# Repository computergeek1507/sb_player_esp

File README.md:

# ESP32-P4 SB Player

An FSEQ sequence player for the ESP32-P4 that drives holiday and animated light displays. Reads `.fseq` v2 files from an SD card and streams channel data out over E1.31 (sACN) and/or DDP to LED controllers, with synchronized audio playback and a time-based scheduler.

## Downloads

Rolling builds of `main`, updated automatically by GitHub Actions on every push:

- **Firmware** - [firmware-latest](https://github.com/computergeek1507/sb_player_esp/releases/tag/firmware-latest): `SBPlayer.ino.bin` (update), `littlefs.bin` (web pages), `SBPlayer.ino.merged.bin` (first flash over USB)
- **SB Card Builder** - [builder-latest](https://github.com/computergeek1507/sb_player_esp/releases/tag/builder-latest): Flutter and Qt Windows apps, and the Python script; the web version is at <https://computergeek1507.github.io/sb_player_esp/>

## Features

- **FSEQ v2 playback** — reads uncompressed sequences from SD card, frame-accurate timing via FreeRTOS tasks
- **E1.31 (sACN) output** — up to 8 outputs, unicast or multicast, configurable universe/channel mapping
- **DDP output** — up to 8 outputs with per-output channel mapping
- **Audio playback** — WAV and MP3 via I2S DAC (PCM5102A / UDA1334A), auto-matched from sequence media field
- **MultiSync** — master mode to keep secondary players frame-synced
- **Scheduler** — time-windowed autoplay with named playlists; repeat and shuffle support
- **Wired Ethernet** — DHCP or static IP; NTP time sync
- **WiFi AP** — always-on access point for configuration (`SB-Player` / `sbplayer` by default)
- **Web UI** — browser-based management for config, outputs, sequences, playlists, schedule, and OTA firmware updates
- **OLED status display** — 128×64 SSD1306 shows IP, current sequence, frame progress, FPS, and audio state
- **RTC support** — DS3231, DS1307, or PCF8523 for accurate scheduling without NTP; NTP writes back to RTC on first sync

## Repository Layout

```
firmware/SBPlayer/       Arduino sketch and headers
  SBPlayer.ino           Main sketch: setup, playback task, audio task, loop
  config.h               Device config struct + JSON load/save
  fseq.h                 FSEQ v2 parser
  audio.h                I2S audio player (WAV/MP3)
  e131.h                 E1.31/sACN sender
  ddp.h                  DDP sender
  multisync.h            FPP MultiSync master
  scheduler.h            Time-based scheduler + playlist engine
  oled.h                 SSD1306 OLED driver
  rtc.h                  RTC abstraction (DS3231/DS1307/PCF8523)
  sdupdate.h             Firmware / web pages update from the SD card at boot
  webui.h                Async HTTP + WebSocket API and web UI
  data/                  LittleFS web pages (config, outputs, sequences,
                          playlists, schedule, OTA)

hardware/                KiCad ( PCB project (ESP32-P4 + OLED, I2S audio and RTC carrier)
  ESP32-P4_OLED.*        Schematic, PCB, project files
  jlcpcb/                JLCPCB-ready gerbers, BOM, and CPL

tools/                   SB Card Builder (prepares the SD card from xLights)
  sb_card_builder.py     Python / Tkinter version (GUI + command line)
  sb_card_builder_flutter/  Flutter version (Windows desktop and web)
  sb_card_builder_qt/    C++ / Qt 6 version (GUI + command line)
  icon/                  App icon and the script that generates it
```

## Hardware

The carrier board breaks out:

| Connector | Purpose |
|-----------|---------|
| J1 (2×13) | ESP32-P4 module |
| J2 (1×4)  | I2C OLED (SSD1306) |
| J3 (1×6)  | I2S DAC (UDA1334A pin-compatible) |
| J4 (1×6)  | I2S DAC (PCM5102A pin-compatible) |
| U3        | PCF8523T RTC with 32.768 kHz crystal |
| U2        | CR1220 RTC battery backup |

Production files for JLCPCB are in `hardware/jlcpcb/`.

## Firmware Setup

**Board**: `esp32:esp32:esp32p4` (Arduino ESP32 core 3.x)

**Required libraries** (install via Arduino Library Manager or clone into `~/Arduino/libraries`):
- ESP Async WebServer (ESP32Async) and Async TCP
- ArduinoJson
- ESP8266Audio (provides `AudioFileSourceSD`, `AudioGeneratorWAV/MP3`, `AudioOutputI2S`; supports ESP32)
- Adafruit GFX Library
- Adafruit SSD1306
- RTClib

The GitHub Actions workflow `.github/workflows/firmware.yml` builds the firmware with arduino-cli (ESP32 core 3.3.8, default partition scheme) and a `littlefs.bin` of the web pages; both are attached to each run as the `SBPlayer-firmware` download.

**Build and flash**:
1. Open `firmware/SBPlayer/SBPlayer.ino` in Arduino IDE
2. Select board `ESP32P4 Dev Module` and your port
3. Flash the sketch
4. Flash the LittleFS filesystem image (`littlefs.bin`) using the ESP32 LittleFS upload tool — this deploys the web UI pages

## SD Card Layout

```
/sequences/      FSEQ v2 sequence files + matching audio (*.wav / *.mp3)
/playlists/      JSON playlist files
schedule.json    Active schedule (created/managed via web UI)
firmware.bin     Optional firmware update (SBPlayer.ino.bin), installed at boot
littlefs.bin     Optional web pages update (LittleFS image), installed at boot
update.log       Result of each update the player installed from the card
```

**Updating from the SD card** — at boot the player flashes `/littlefs.bin` and then `/firmware.bin` if they are on the card, renames each to `*.installed.bin` (or `*.failed.bin`, so a bad file is only tried once), appends the result to `/update.log` and restarts. `config.json` and `outputs.json` are kept across a web pages update. Use `SBPlayer.ino.bin`, not `SBPlayer.ino.merged.bin` (the merged image is for a full USB flash). The SB Card Builder's *Player update* tab, or `--firmware` / `--littlefs` on the command line, checks the files and copies them to the card. Updates can also be uploaded over the network from `/ota.html`.

Example `schedule.json`:
```json
{
  "entries": [
    { "days": 127, "start_hour": 18, "start_min": 0,
      "end_hour": 23, "end_min": 0, "playlist": "default.json" }
  ]
}
```

Example `playlists/default.json`:
```json
{ "repeat": true, "shuffle": false, "entries": ["show1.fseq", "show2.fseq"] }
```

## SB Card Builder

`tools/sb_card_builder.py` prepares the SD card from an xLights show folder (Python 3.9+, Tkinter):

```
python tools/sb_card_builder.py                                   # GUI
python tools/sb_card_builder.py --show <show folder> --out <SD>   # command line
```

- **Outputs** — reads `xlights_networks.xml` and writes `outputs.json` (E1.31 and DDP controllers). The player imports this file from the card on the next boot and renames it to `outputs.imported.json`.
- **Sequences** — converts xLights `.fseq` files (zstd / zlib compressed, sparse, v1 or v2) to the uncompressed FSEQ v2 the player reads, and copies the matching `.mp3` / `.wav` into `/sequences`.
- **Playlists / Schedule** — builds `playlists/*.json` and `schedule.json`.
- **Player update** — copies a firmware image (`SBPlayer.ino.bin`) and/or web pages image (`littlefs.bin`) to the card root, after checking that each is the right kind of image for the ESP32-P4; the player installs them at its next boot. Command line: `--firmware <bin>` and `--littlefs <bin>` with `--out`.
- **SB Pixel 16 export** — writes sequences for an [SB Pixel 16](https://github.com/computergeek1507/sb_pixel_16) controller instead: pick it under *Export for* on the Sequences tab, or use `--pixel16 <controller name>` with `--show` and `--out`. Each file holds only that controller's channels, uncompressed, in `/sequences`; no audio, `outputs.json`, playlists or schedule are written, because that controller just loops the folder. For an E1.31 controller (or DDP without *Keep Channel Numbers*) the channels are renumbered from 1, matching the port start channels used for E1.31. For DDP with *Keep Channel Numbers* they keep their xLights numbers (stored as one sparse range). The controller buffers at most 262,144 channels per frame and plays the first 64 files.

zstd-compressed sequences (the xLights default) need `python -m pip install zstandard` on Python older than 3.14.

The same tool also exists in two other forms. All three write identical files.

**Flutter (Windows desktop and web)** — `tools/sb_card_builder_flutter`, needs the Flutter SDK:

```
cd tools/sb_card_builder_flutter
flutter run -d windows            # or: flutter build windows  -> build\windows\x64\runner\Release\
flutter run -d chrome             # or: flutter build web      -> build\web\
```

The web build reads and writes folders through the File System Access API, so it needs Chrome or Edge on a computer, served from `localhost` or https. The Flutter app uses the same dark color scheme as the player's web UI.

The web version is deployed to GitHub Pages by `.github/workflows/sb_card_builder_flutter.yml` on every push to `main` that changes the Flutter app: <https://computergeek1507.github.io/sb_player_esp/>.

To host the web build on your own web server instead:

```
flutter build web --release --base-href /sbcard/   # path it will be served from; omit for the site root
```

Copy everything in `build\web\` to that path on the server. The server must use https, and should serve `.wasm` as `application/wasm`. Send `index.html`, `flutter_bootstrap.js` and `flutter_service_worker.js` with `Cache-Control: no-cache` so visitors get new versions after an upload.

**C++ (Qt 6 Widgets)** — `tools/sb_card_builder_qt`, needs Qt 6, CMake 3.21+ and a C++17 compiler; zstd, nlohmann/json and pugixml are downloaded during configure:

```
cd tools/sb_card_builder_qt
cmake -S . -B build -DCMAKE_PREFIX_PATH=<Qt kit, e.g. D:/Qt/6.8.3/msvc2022_64>
cmake --build build --config Release
build\Release\sb_card_builder.exe                               # GUI
build\Release\sb_card_cli.exe --show <show folder> --out <SD>   # command line
```

## Default Pin Assignments

| Function | GPIO |
|----------|------|
| I2S BCLK | 26 |
| I2S LRCLK | 25 |
| I2S DATA | 22 |
| OLED SDA / RTC SDA | 7 |
| OLED SCL / RTC SCL | 8 |
| Ethernet PHY addr | 1 |
| Ethernet MDC | 31 |
| Ethernet MDIO | 52 |
| Ethernet power | 51 |

All pins are configurable via the web UI.

## Web UI Endpoints

| Path | Description |
|------|-------------|
| `/` | Dashboard — playback status, play/stop |
| `/config.html` | Device settings (network, audio, RTC, hostname) |
| `/outputs.html` | E1.31 and DDP output configuration |
| `/sequences.html` | Browse and play sequences from SD |
| `/playlists.html` | Manage playlists |
| `/schedule.html` | Time-based schedule editor |
| `/ota.html` | OTA firmware update |
| `/api/status` | JSON playback status (also pushed via WebSocket `/ws`) |

## License

[CC BY-NC 4.0](LICENSE) — free for personal and non-commercial use; commercial use is not permitted.

## First Boot

1. Connect to the `SB-Player` WiFi AP (password `sbplayer`)
2. Open `http://192.168.4.1` in a browser
3. Configure Ethernet, NTP timezone, output universes, and I2S pins
4. Copy sequences to the SD card and create a playlist
5. Add a schedule entry or play sequences manually from the UI

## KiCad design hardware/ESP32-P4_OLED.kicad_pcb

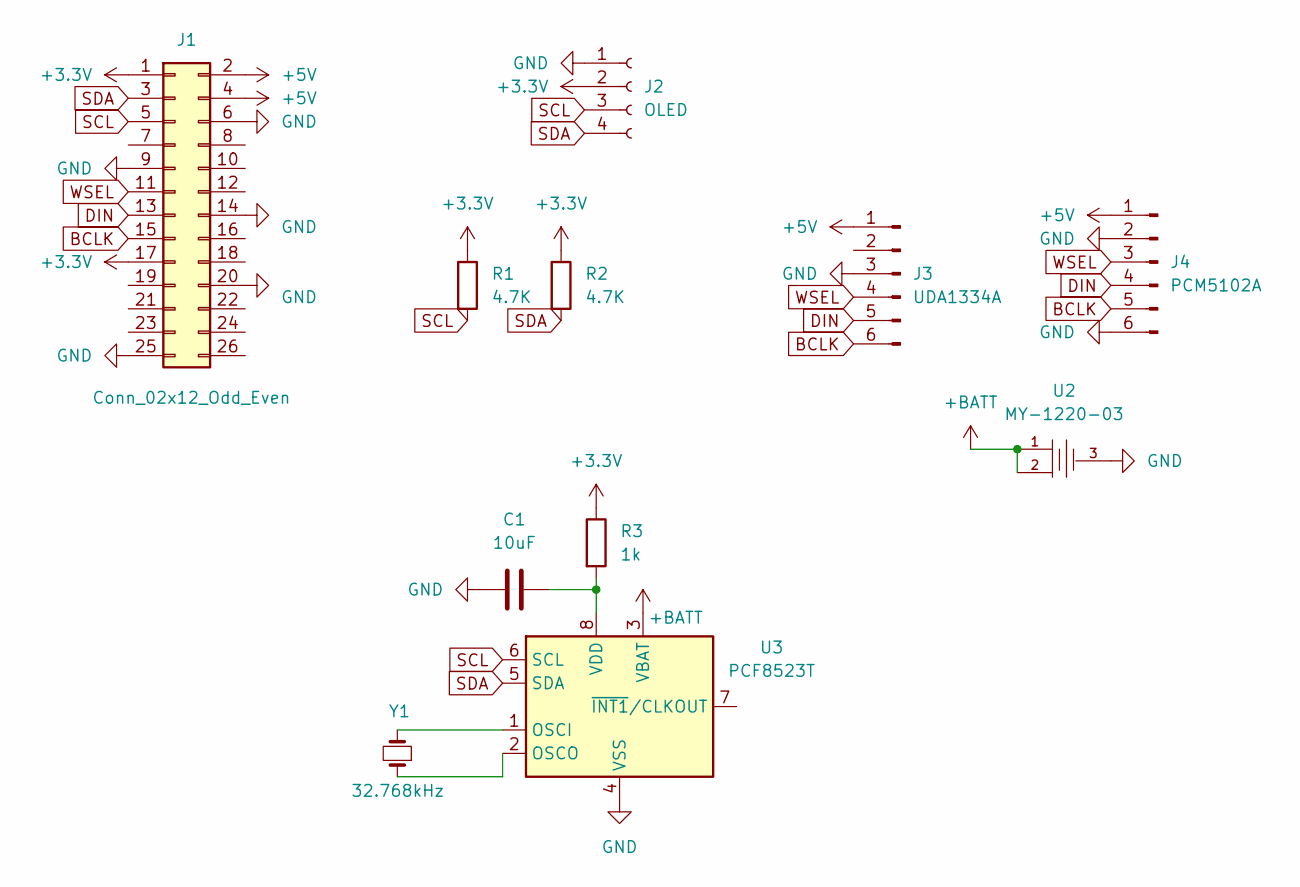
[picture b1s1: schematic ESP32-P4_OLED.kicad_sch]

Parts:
C1: 10uF; C_0805_2012Metric
J1: Conn_02x12_Odd_Even; PinSocket_2x13_P2.54mm_Vertical
J2: OLED; PinSocket_1x04_P2.54mm_Vertical
J3: UDA1334A; PinHeader_1x06_P2.54mm_Vertical
J4: PCM5102A; PinHeader_1x06_P2.54mm_Vertical
R1, R2: 4.7K; R_0603_1608Metric
R3: 1k; R_0603_1608Metric
U2: MY-1220-03; BAT-SMD_MY-1220-03; LCSC C964818
U3: PCF8523T; SOIC-8_3.9x4.9mm_P1.27mm
Y1: 32.768kHz; FC-135R_L3.2-W1.5

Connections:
+3.3V: J1.1, J1.17, J2.2, R1.1, R2.1, R3.1
+5V: J1.2, J1.4, J3.1, J4.1
+BATT: U2.1 (+), U2.2 (+), U3.3 (VBAT)
BCLK: J1.15, J3.6, J4.5
DIN: J1.13, J3.5, J4.4
GND: C1.1, J1.6, J1.9, J1.14, J1.20, J1.25, J2.1, J3.3, J4.2, J4.6, U2.3 (-), U3.4 (VSS)
unnamed: U3.1 (OSCI), Y1.2
unnamed: U3.2 (OSCO), Y1.1
unnamed: C1.2, R3.2, U3.8 (VDD)
SCL: J1.5, J2.3, R1.2, U3.6 (SCL)
SDA: J1.3, J2.4, R2.2, U3.5 (SDA)
WSEL: J1.11, J3.4, J4.3

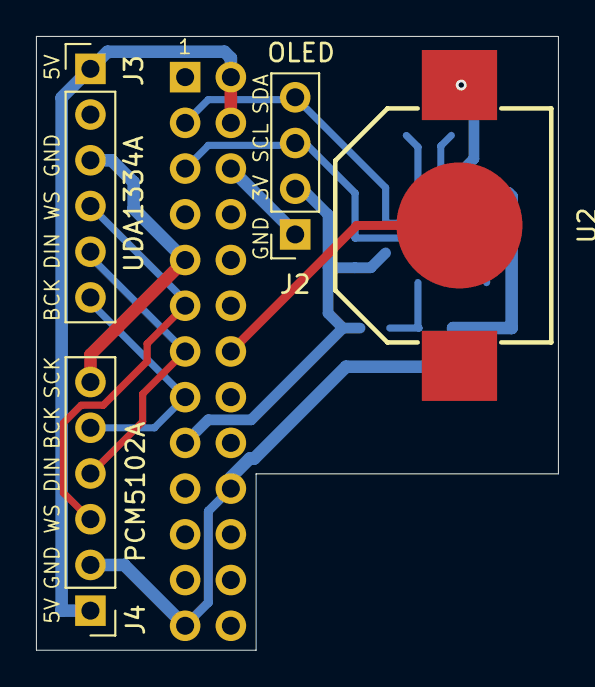
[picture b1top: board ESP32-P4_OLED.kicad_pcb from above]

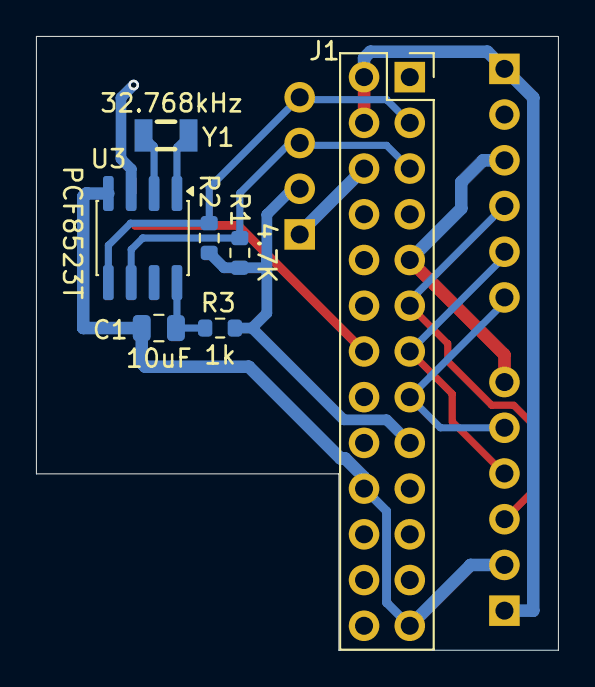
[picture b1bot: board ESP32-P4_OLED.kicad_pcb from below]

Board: 2 copper layers, 29.0 x 34.1 mm, 11 parts (7 on the bottom side), 12 nets.

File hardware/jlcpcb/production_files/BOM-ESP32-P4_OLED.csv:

Comment,Designator,Footprint,LCSC,Quantity
10uF,C1,C_0805_2012Metric,C15850,1
1k,R3,R_0603_1608Metric,C21190,1
32.768kHz,Y1,FC-135R_L3.2-W1.5,C32346,1
4.7K,"R1,R2",R_0603_1608Metric,C23162,2
MY-1220-03,U2,BAT-SMD_MY-1220-03,C964818,1
PCF8523T,U3,SOIC-8_3.9x4.9mm_P1.27mm,C2651516,1
PCM5102A,J4,PinHeader_1x06_P2.54mm_Vertical,,1
UDA1334A,J3,PinHeader_1x06_P2.54mm_Vertical,,1
OLED,J2,PinSocket_1x04_P2.54mm_Vertical,,1
Conn_02x12_Odd_Even,J1,PinSocket_2x13_P2.54mm_Vertical,,1

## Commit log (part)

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2026-05-17 add firmware
2026-05-17 add sb player
2026-05-17 add license
